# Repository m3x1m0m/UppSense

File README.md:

UppSense17- Open Source sensor for chemical analysis based on fuoresence.
 
## Hardware

The hardware consists out of three PCBs so far: An analog PCB, a digital PCB and an active Backplane. Two PCBs are developed with KiCAD. One is developed with Altium.

A transimpedance amplifier is used to convert light into a voltage. With a
second stage this voltage is amplified. Both outputs are available for the ADC. 

On the digital board there is besides an ESP8266, an ADC, a DAC and a temperature
sensor. The DAC is needed to steer the LED driver circuit, that excites the
sample. 
 
## Software

The software is written in C++ leveraging the
[Sming](https://github.com/SmingHub/Sming) framework. This enables IoT
applications very easily.

In the UML diagram above it is examplarily shown how the software works. Providers
and receivers can be tied together in pairs to enable an easy way to exchange
data. 

[Software Documentation](http://uppsense.eu/swdoc/)

## Web & Contact
Website: www.uppsense.eu | Email: contact@uppsense.eu

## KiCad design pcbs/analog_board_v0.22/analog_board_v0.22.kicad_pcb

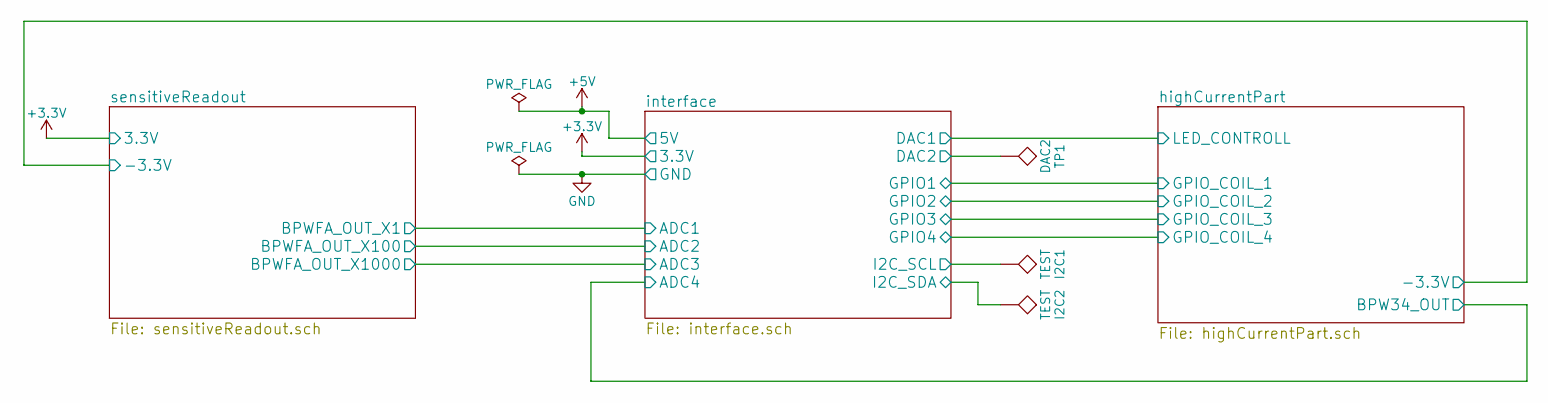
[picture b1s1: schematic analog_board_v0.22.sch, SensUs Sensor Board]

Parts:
I2C1, I2C2: TEST; TP_SMD_quadr_1mm
TP1: DAC2; TP_SMD_quadr_1mm

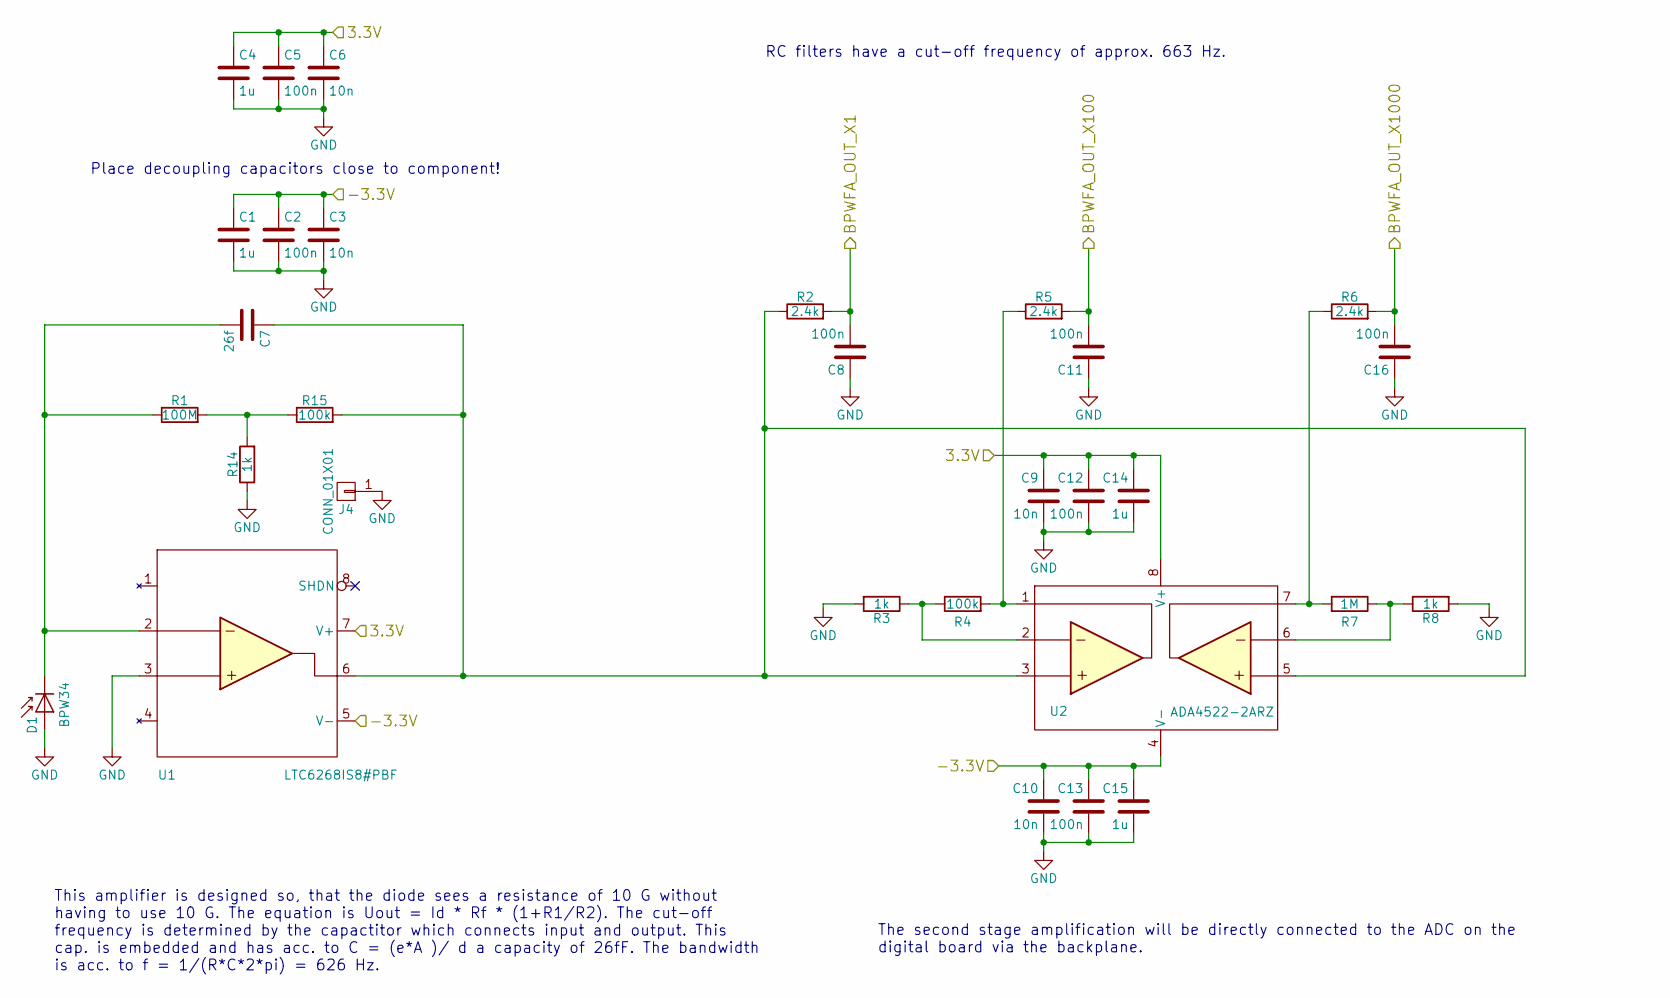
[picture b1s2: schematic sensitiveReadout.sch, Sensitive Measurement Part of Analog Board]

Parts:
C1, C4, C14, C15: 1u; R_0805; Farnell 2496946
C2, C5, C8, C11, C12, C13, C16: 100n; R_0805; Farnell 499687
C3, C6, C9, C10: 10n; R_0805; Farnell 1414662
C7: 26f; EMBEDDED_CAP_1mm
D1: BPW34; BPW34FA_w_Silks; Farnell 1045425
J4: CONN_01X01; GuardConnector
R1: 100M; R_0805_W_Silks; Farnell 9236511
R2, R5, R6: 2.4k; R_0805; Farnell 2502703
R3, R8: 1k; R_0805; Farnell 9237496
R4: 100k; R_0805; Farnell 2447551
R7: 1M; R_0805; Farnell 1576507
R14: 1k; R_0805_W_Silks; Farnell 9237496
R15: 100k; R_0805_W_Silks; Farnell 2447551
U1: LTC6268IS8#PBF; SOIC-8-N-W-Silks; Farnell 2464182
U2: ADA4522-2ARZ; SOIC-8-N; Farnell 2505560

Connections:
+3V3: C4.1, C5.1, C6.1, C9.1, C12.1, C14.1, U1.7 (V+), U2.8 (V+); also elsewhere on the board
/highCurrentPart/-3.3V: C1.1, C2.1, C3.1, C10.1, C13.1, C15.1, U1.5 (V-), U2.4 (V-); also elsewhere on the board
/interface/ADC1: C8.2, R2.2; also elsewhere on the board
/interface/ADC2: C11.2, R5.2; also elsewhere on the board
/interface/ADC3: C16.2, R6.2; also elsewhere on the board
GND: C1.2, C2.2, C3.2, C4.2, C5.2, C6.2, C8.1, C9.2, C10.2, C11.1, C12.2, C13.2, C14.2, C15.2, C16.1, D1.2 (A), J4.1, R3.2, R8.2, R14.1, U1.3; also elsewhere on the board
unnamed: C7.1, R2.1, R15.2, U1.6, U2.3, U2.5
unnamed: C7.2, D1.1 (K), R1.1, U1.2
unnamed: R1.2, R14.2, R15.1
unnamed: R3.1, R4.1, U2.2
unnamed: R4.2, R5.1, U2.1
unnamed: R6.1, R7.2, U2.7
unnamed: R7.1, R8.1, U2.6

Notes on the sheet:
Place decoupling capacitors close to component!
The second stage amplification will be directly connected to the ADC on the digital board via the backplane.
RC filters have a cut-off frequency of approx. 663 Hz.
This amplifier is designed so, that the diode sees a resistance of 10 G without having to use 10 G. The equation is Uout = Id * Rf * (1+R1/R2). The cut-off frequency is determined by the capactitor which connects input and output. This cap. is embedded and has acc. to C = (e*A )/ d a capacity of 26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

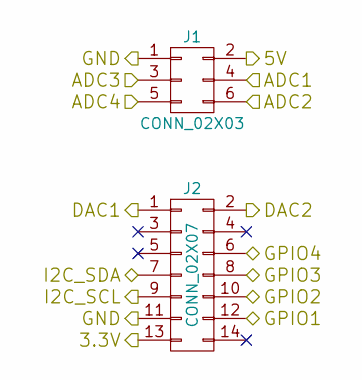
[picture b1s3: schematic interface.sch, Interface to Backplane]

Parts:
J1: CONN_02X03; Pin_Header_Angled_2x03_Pitch2.54mm
J2: CONN_02X07; Pin_Header_Angled_2x07_Pitch2.54mm

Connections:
+3V3: J2.13; also elsewhere on the board
+5V: J1.2; also elsewhere on the board
/interface/ADC1: J1.4; also elsewhere on the board
/interface/ADC2: J1.6; also elsewhere on the board
/interface/ADC3: J1.3; also elsewhere on the board
/interface/ADC4: J1.5; also elsewhere on the board
/interface/DAC1: J2.1; also elsewhere on the board
/interface/DAC2: J2.2; also elsewhere on the board
/interface/GPIO1: J2.12; also elsewhere on the board
/interface/GPIO2: J2.10; also elsewhere on the board
/interface/GPIO3: J2.8; also elsewhere on the board
/interface/GPIO4: J2.6; also elsewhere on the board
/interface/I2C_SCL: J2.9; also elsewhere on the board
/interface/I2C_SDA: J2.7; also elsewhere on the board
GND: J1.1, J2.11; also elsewhere on the board

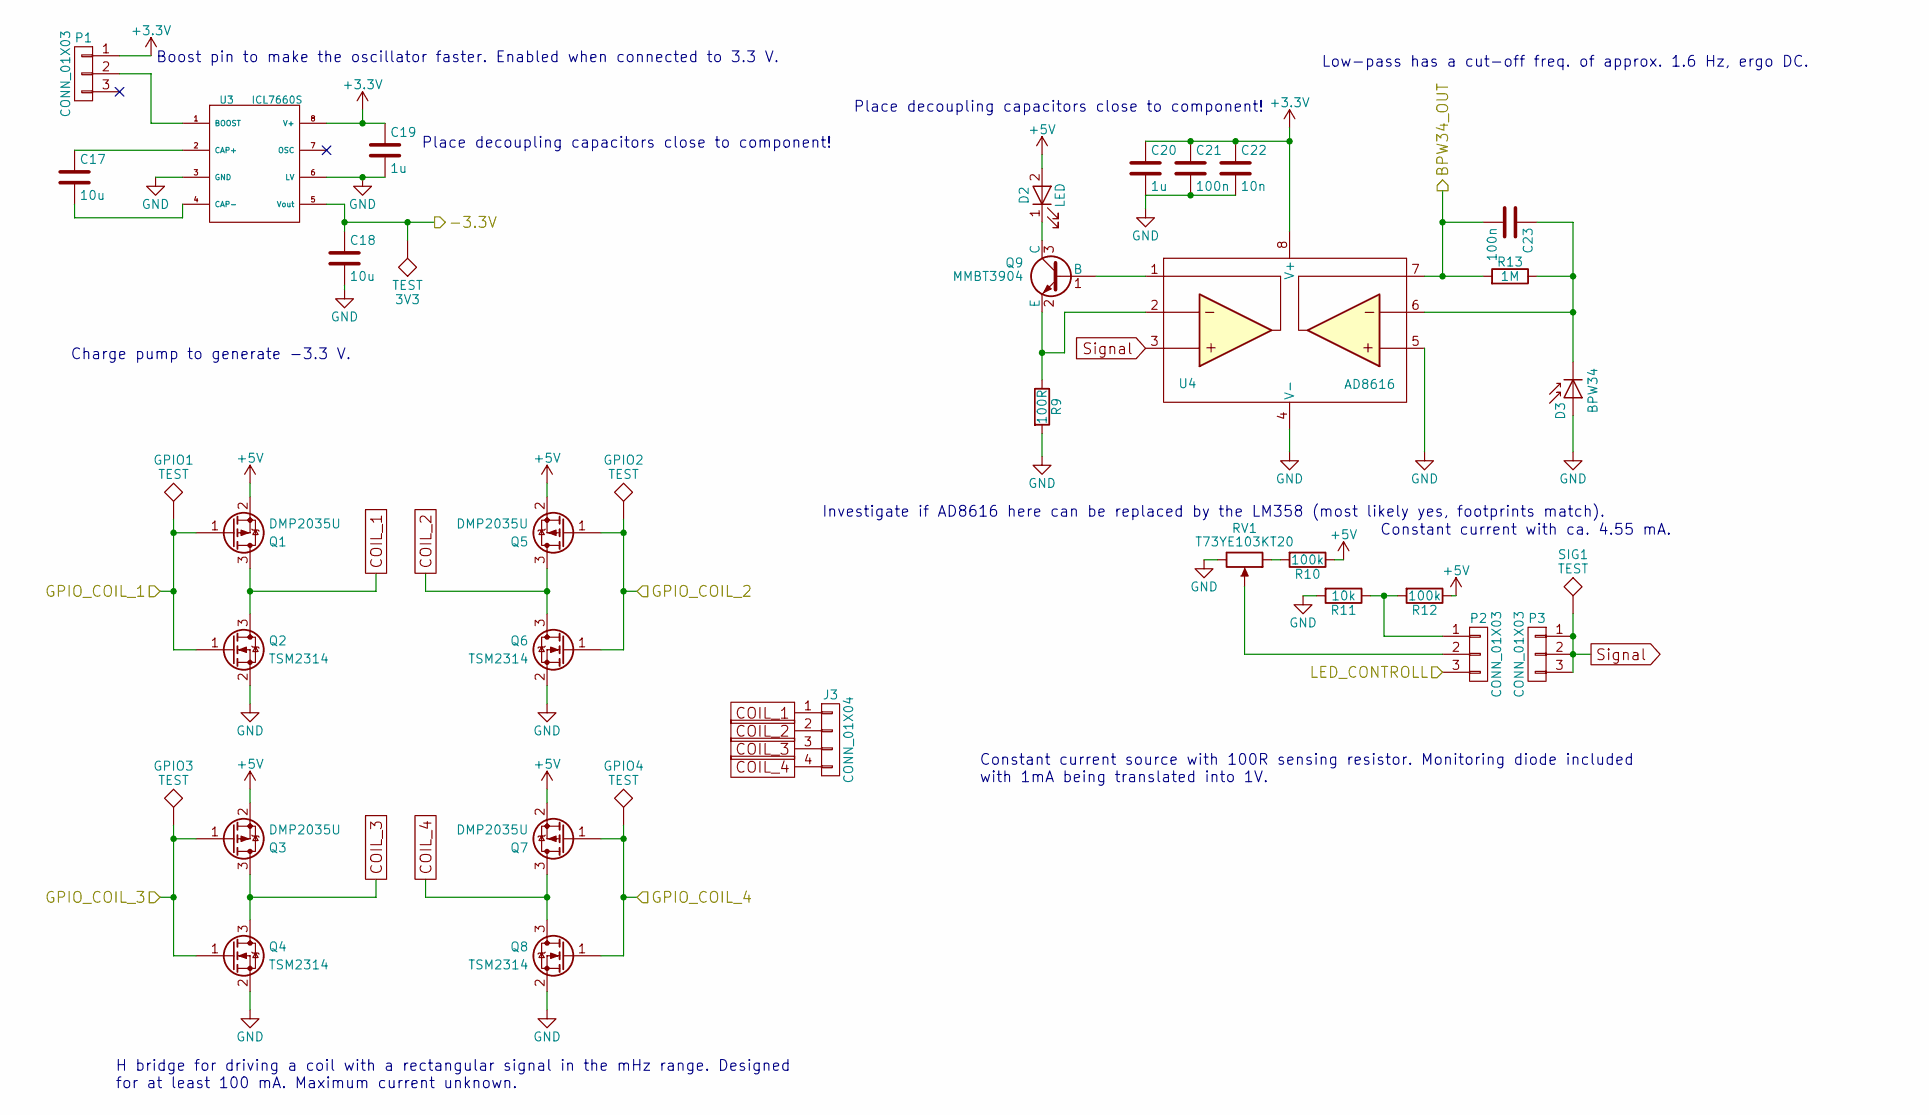
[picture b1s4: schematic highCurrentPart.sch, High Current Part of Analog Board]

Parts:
3V3: TEST; TP_SMD_quadr_1mm
C17, C18: 10u; R_0805; Farnell 1833812
C19: 1u; R_0805; Farnell 1845751
C20: 1u; R_0805; Farnell 2496946
C21, C23: 100n; R_0805; Farnell 499687
C22: 10n; R_0805; Farnell 1414662
D2: LED; LED_D5.0mm
D3: BPW34; BPW34FA; Farnell 1045425
GPIO1, GPIO2, GPIO3, GPIO4: TEST; TP_SMD_quadr_1mm
J3: CONN_01X04; LED_CONN_1.25_PITCH
P1, P2, P3: CONN_01X03; Samtec-PHT-1-3-01-L-S
Q1, Q3, Q5, Q7: DMP2035U; SOT-23; Farnell 2061419
Q2, Q4, Q6, Q8: TSM2314; SOT-23; Farnell 1864589
Q9: MMBT3904; SOT-23; Farnell 1757935
R9: 100R; R_0805; Farnell 1632456
R10, R12: 100k; R_0805; Farnell 2447551
R11: 10k; R_0805; Farnell 9237755
R13: 1M; R_0805; Farnell 1576507
RV1: T73YE103KT20; Vishay_T73YE103KT20; Farnell 2550676
SIG1: TEST; TP_SMD_quadr_1mm
U3: ICL7660S; SOIC-8-N; Farnell 1561969
U4: AD8616; SOIC-8-N; Farnell 1581952

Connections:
+3V3: C19.1, C20.1, C21.1, C22.1, P1.1, U3.8 (V+), U4.8 (V+); also elsewhere on the board
+5V: D2.2 (A), Q1.2 (S), Q3.2 (S), Q5.2 (S), Q7.2 (S), R10.1, R12.1; also elsewhere on the board
/highCurrentPart/-3.3V: 3V3.1, C18.1, U3.5 (Vout); also elsewhere on the board
/interface/ADC4: C23.2, R13.2, U4.7; also elsewhere on the board
/interface/DAC1: P2.3; also elsewhere on the board
/interface/GPIO1: GPIO1.1, Q1.1 (G), Q2.1 (G); also elsewhere on the board
/interface/GPIO2: GPIO2.1, Q5.1 (G), Q6.1 (G); also elsewhere on the board
/interface/GPIO3: GPIO3.1, Q3.1 (G), Q4.1 (G); also elsewhere on the board
/interface/GPIO4: GPIO4.1, Q7.1 (G), Q8.1 (G); also elsewhere on the board
COIL_1: J3.1, Q1.3 (D), Q2.3 (D)
COIL_2: J3.2, Q5.3 (D), Q6.3 (D)
COIL_3: J3.3, Q3.3 (D), Q4.3 (D)
COIL_4: J3.4, Q7.3 (D), Q8.3 (D)
GND: C18.2, C19.2, C20.2, C21.2, C22.2, D3.2 (A), Q2.2 (S), Q4.2 (S), Q6.2 (S), Q8.2 (S), R9.2, R11.2, RV1.3, U3.3 (GND), U3.6 (LV), U4.4 (V-), U4.5; also elsewhere on the board
unnamed: C17.1, U3.2 (CAP+)
unnamed: C17.2, U3.4 (CAP-)
unnamed: C23.1, D3.1 (K), R13.1, U4.6
unnamed: D2.1 (K), Q9.3 (C)
unnamed: P1.2, U3.1 (BOOST)
unnamed: P2.1, R11.1, R12.2
unnamed: P2.2, RV1.2
unnamed: Q9.1 (B), U4.1
unnamed: Q9.2 (E), R9.1, U4.2
unnamed: R10.2, RV1.1
Signal: P3.1, P3.2, P3.3, SIG1.1, U4.3; also elsewhere on the board

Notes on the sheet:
Place decoupling capacitors close to component!
Constant current source with 100R sensing resistor. Monitoring diode included with 1mA being translated into 1V.
Constant current with ca. 4.55 mA.
H bridge for driving a coil with a rectangular signal in the mHz range. Designed for at least 100 mA. Maximum current unknown.
Boost pin to make the oscillator faster. Enabled when connected to 3.3 V.
Charge pump to generate -3.3 V.
Low-pass has a cut-off freq. of approx. 1.6 Hz, ergo DC.
Investigate if AD8616 here can be replaced by the LM358 (most likely yes, footprints match).

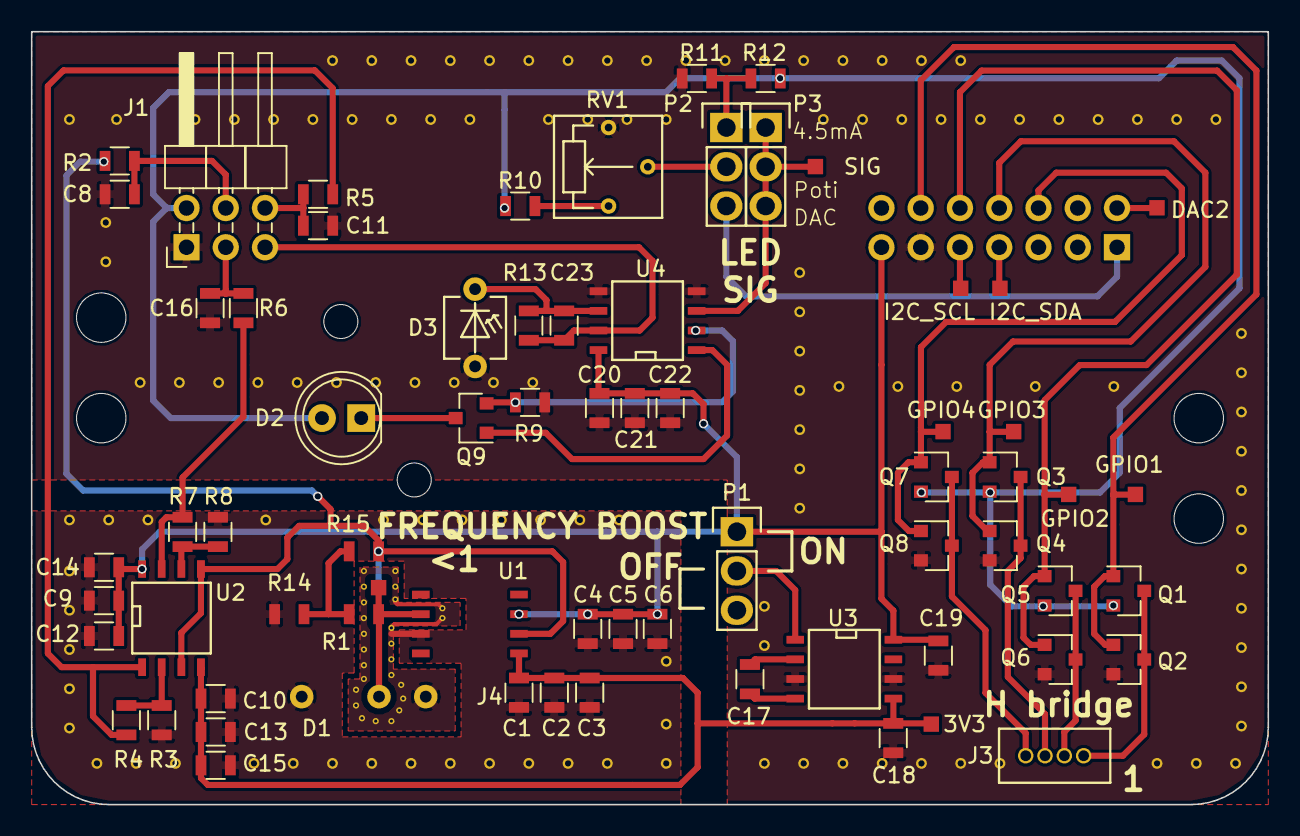
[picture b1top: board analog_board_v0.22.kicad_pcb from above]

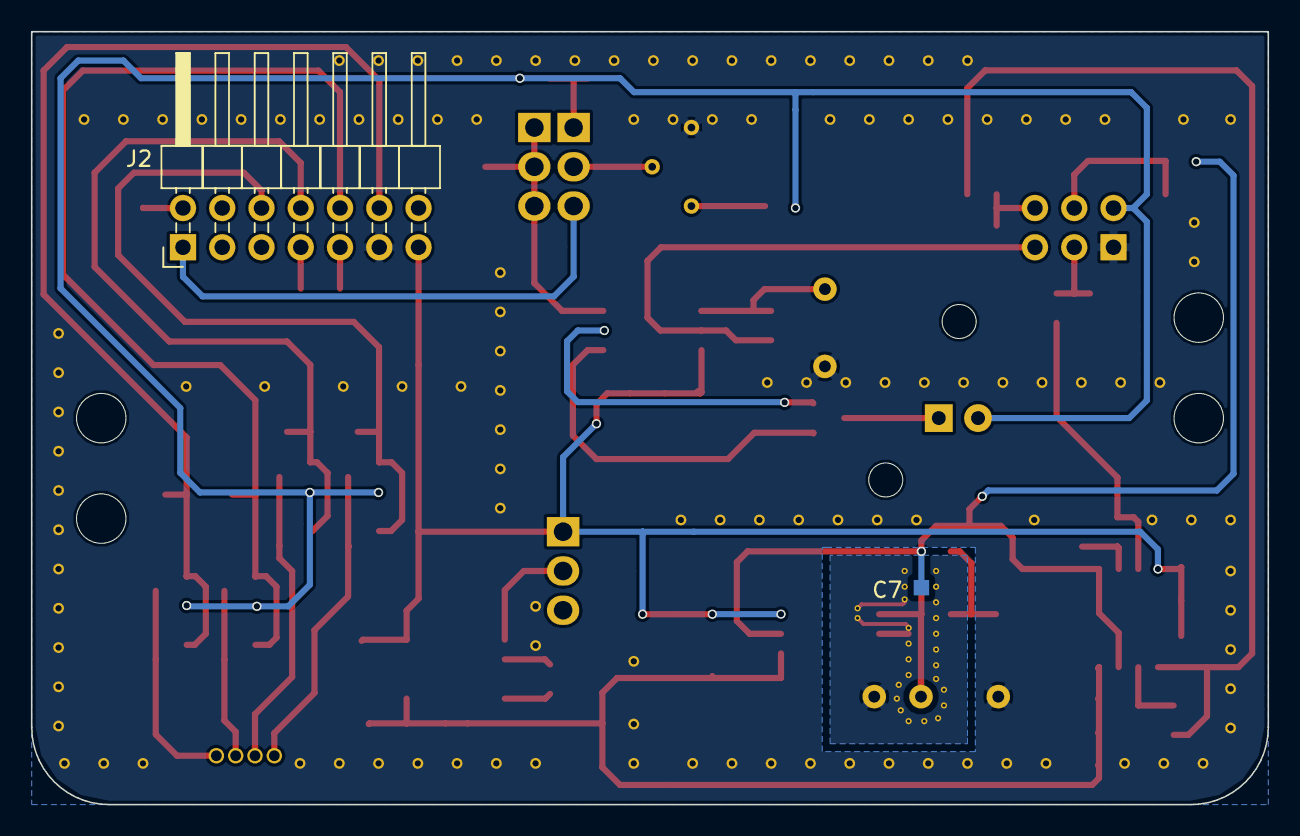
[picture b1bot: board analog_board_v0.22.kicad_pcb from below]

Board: 2 copper layers, 80.0 x 50.0 mm, 71 parts (2 on the bottom side), 38 nets.

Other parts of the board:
DAC2: DAC2; TP_SMD_quadr_1mm
I2C_SCL, I2C_SDA: TEST; TP_SMD_quadr_1mm
SIG: TEST; TP_SMD_quadr_1mm

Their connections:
/interface/DAC2: DAC2.1; also elsewhere on the board
/interface/I2C_SCL: I2C_SCL.1; also elsewhere on the board
/interface/I2C_SDA: I2C_SDA.1; also elsewhere on the board
Signal: SIG.1; also elsewhere on the board

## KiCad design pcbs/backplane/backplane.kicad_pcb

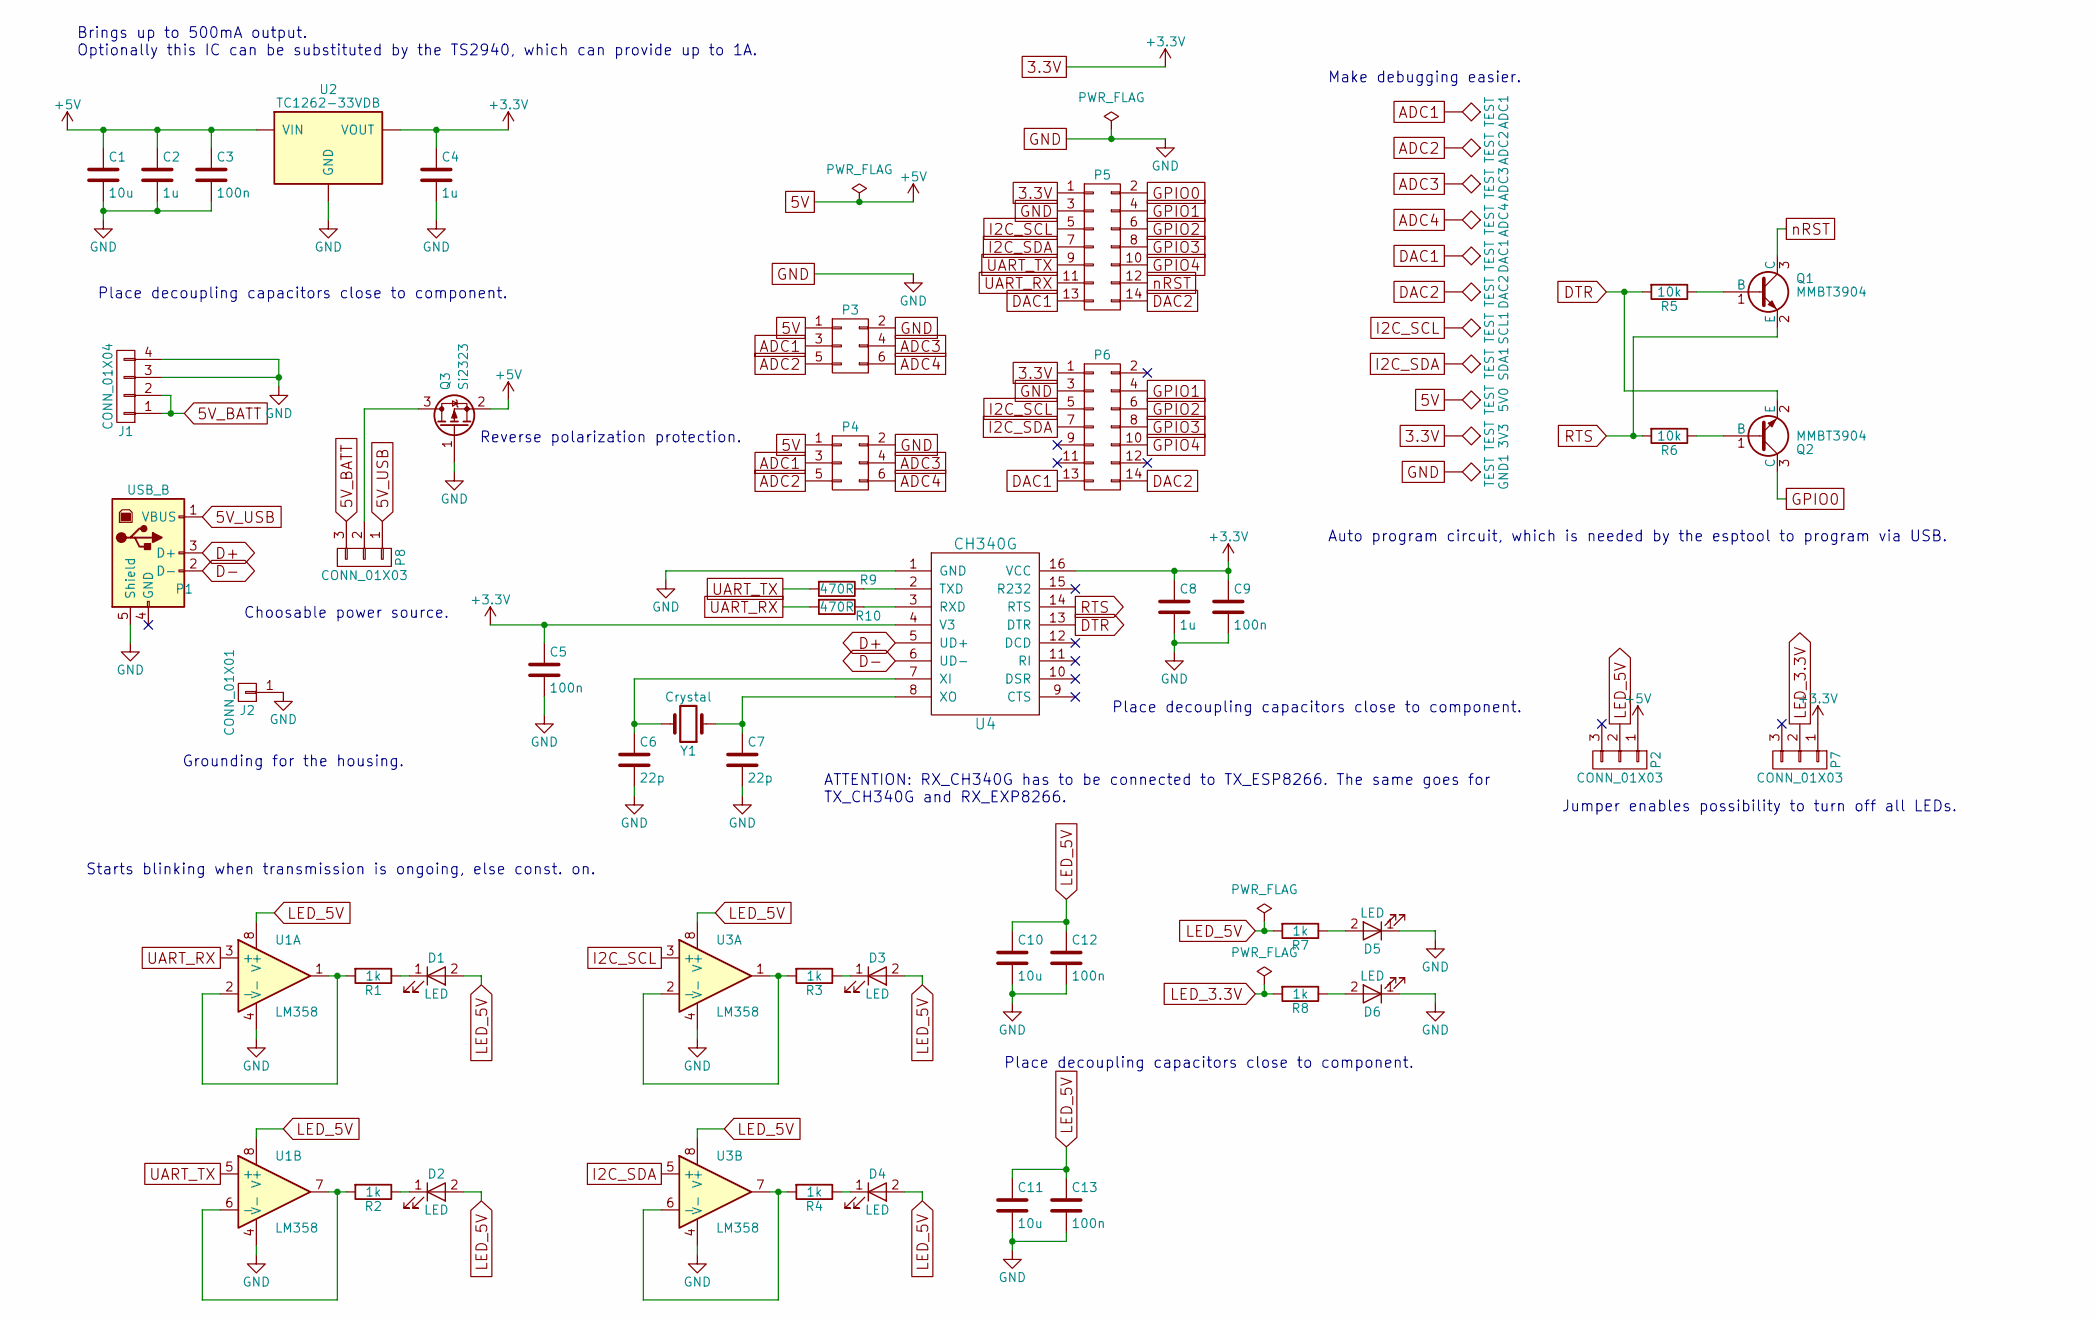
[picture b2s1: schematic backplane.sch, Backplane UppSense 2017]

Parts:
3V3, 5V0: TEST; TP_SMD_quadr_1mm
ADC1, ADC2, ADC3, ADC4: TEST; TP_SMD_quadr_1mm
C1, C10, C11: 10u; R_0805; Farnell 1833812
C2, C4, C8: 1u; R_0805; Farnell 2496946
C3, C5, C9, C12, C13: 100n; R_0805; Farnell 499687
C6, C7: 22p; R_0805; Farnell 1759489
D1, D2, D3, D4, D5, D6: LED; LED_0805; Farnell 1581242
DAC1, DAC2: TEST; TP_SMD_quadr_1mm
GND1: TEST; TP_SMD_quadr_3mm
J1: CONN_01X04; LED_CONN_1.25_PITCH
J2: CONN_01X01; Samtec-PHT-1-1-01-L-S
P1: USB_B; ZX62D-B-5P8(30); Farnell 2554980
P2, P7, P8: CONN_01X03; Samtec-PHT-1-3-01-L-S
P3, P4: CONN_02X03; Pin_Header_Straight_2x03
P5, P6: CONN_02X07; Pin_Header_Straight_2x07
Q1, Q2: MMBT3904; SOT-23; Farnell 2535650
Q3: Si2323; SOT-23; Farnell 1470106
R1, R2, R3, R4, R7, R8: 1k; R_0805; Farnell 9237496
R5, R6: 10k; R_0805; Farnell 9237755
R9, R10: 470R; R_0805; Farnell 2447662
SCL1: TEST; TP_SMD_quadr_1mm
SDA1: TEST; TP_SMD_quadr_1mm
U1, U3: LM358; SOIC-8-N; Farnell 1564331
U2: TC1262-33VDB; SOT-223; Farnell 1296594
U4: CH340G; SO-16-N
Y1: Crystal; Crystal_SMD_HC49-SD; Farnell 9713344

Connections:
3.3V: 3V3.1, C4.1, C5.1, C8.1, C9.1, P5.1, P6.1, P7.1, U2.3 (VOUT), U4.4 (V3), U4.16 (VCC)
5V: 5V0.1, C1.1, C2.1, C3.1, P2.1, P3.1, P4.1, Q3.2 (S), U2.1 (VIN); also elsewhere on the board
5V_BATT: J1.1, J1.2, P8.3
5V_USB: P1.1 (VBUS), P8.1
ADC1: ADC1.1, P3.3, P4.3
ADC2: ADC2.1, P3.5, P4.5
ADC3: ADC3.1, P3.4, P4.4
ADC4: ADC4.1, P3.6, P4.6
D+: P1.3 (D+), U4.5 (UD+)
D-: P1.2 (D-), U4.6 (UD-)
DAC1: DAC1.1, P5.13, P6.13
DAC2: DAC2.1, P5.14, P6.14
DTR: Q2.2 (E), R5.2, U4.13 (DTR)
GND: C1.2, C2.2, C3.2, C4.2, C5.2, C6.2, C7.2, C8.2, C9.2, C10.2, C11.2, C12.2, C13.2, D5.1 (K), D6.1 (K), GND1.1, J1.3, J1.4, J2.1, P1.5 (Shield), P3.2, P4.2, P5.3, P6.3, Q3.1 (G), U1.4 (V-), U2.2 (GND), U2.4 (GND), U3.4 (V-), U4.1 (GND); also elsewhere on the board
GPIO0: P5.2, Q2.3 (C)
GPIO1: P5.4, P6.4
GPIO2: P5.6, P6.6
GPIO3: P5.8, P6.8
GPIO4: P5.10, P6.10
I2C_SCL: P5.5, P6.5, SCL1.1, U3.3 (+); also elsewhere on the board
I2C_SDA: P5.7, P6.7, SDA1.1, U3.5 (+); also elsewhere on the board
LED_3.3V: P7.2, R8.2
LED_5V: C10.1, C11.1, C12.1, C13.1, D1.2 (A), D2.2 (A), D3.2 (A), D4.2 (A), P2.2, R7.2, U1.8 (V+), U3.8 (V+)
unnamed: C6.1, U4.7 (XI), Y1.2
unnamed: C7.1, U4.8 (XO), Y1.1
unnamed: D1.1 (K), R1.1
unnamed: D2.1 (K), R2.1
unnamed: D3.1 (K), R3.1
unnamed: D4.1 (K), R4.1
unnamed: D5.2 (A), R7.1
unnamed: D6.2 (A), R8.1
unnamed: P8.2, Q3.3 (D)
unnamed: Q1.1 (B), R5.1
unnamed: Q2.1 (B), R6.1
unnamed: R1.2, U1.1, U1.2 (-)
unnamed: R2.2, U1.6 (-), U1.7
unnamed: R3.2, U3.1, U3.2 (-)
unnamed: R4.2, U3.6 (-), U3.7
unnamed: R9.1, U4.2 (TXD)
unnamed: R10.1, U4.3 (RXD)
RTS: Q1.2 (E), R6.2, U4.14 (RTS)
UART_RX: P5.11, R10.2, U1.3 (+)
UART_TX: P5.9, R9.2, U1.5 (+)
nRST: P5.12, Q1.3 (C)

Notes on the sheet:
Place decoupling capacitors close to component.
Brings up to 500mA output. Optionally this IC can be substituted by the TS2940, which can provide up to 1A.
Auto program circuit, which is needed by the esptool to program via USB.
Starts blinking when transmission is ongoing, else const. on.
Make debugging easier.
Jumper enables possibility to turn off all LEDs.
ATTENTION: RX_CH340G has to be connected to TX_ESP8266. The same goes for TX_CH340G and RX_EXP8266.
Reverse polarization protection.
Choosable power source.
Grounding for the housing.

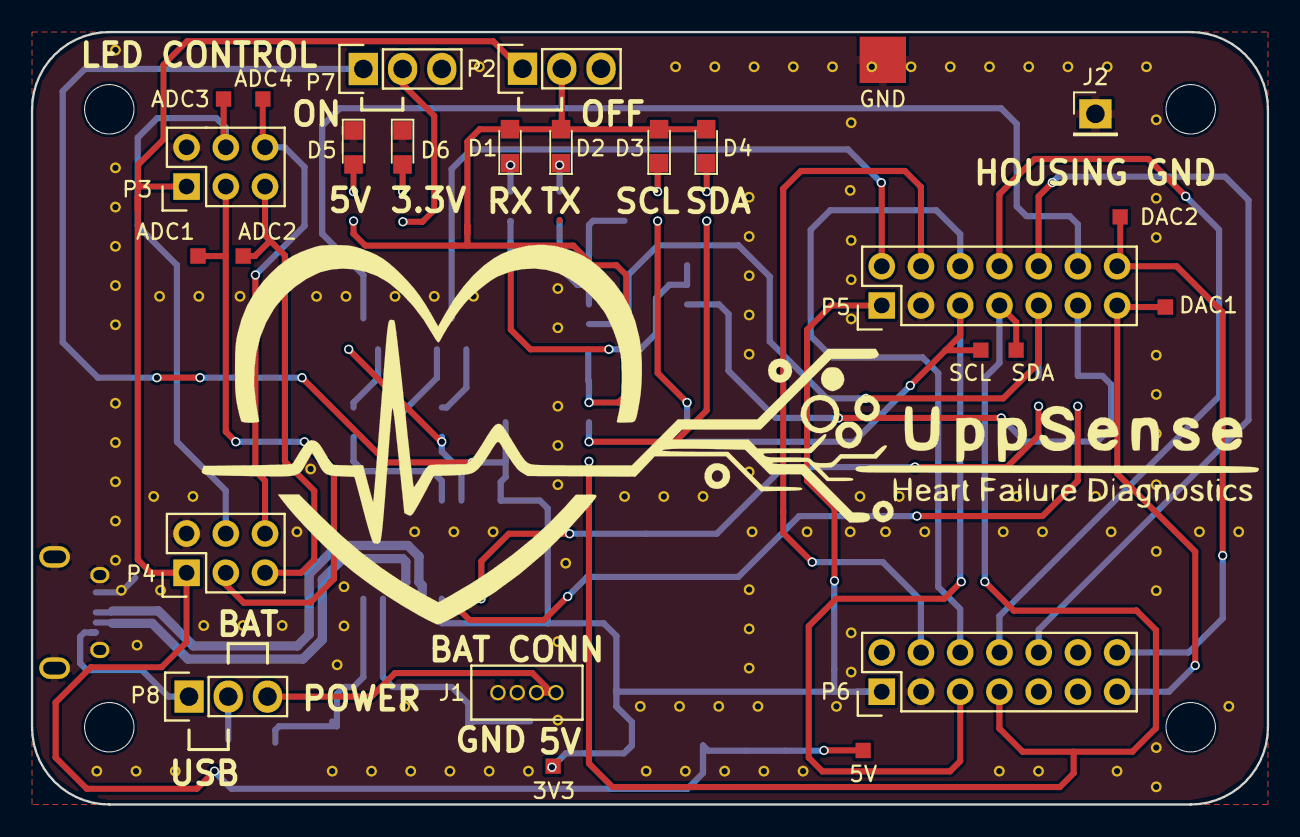
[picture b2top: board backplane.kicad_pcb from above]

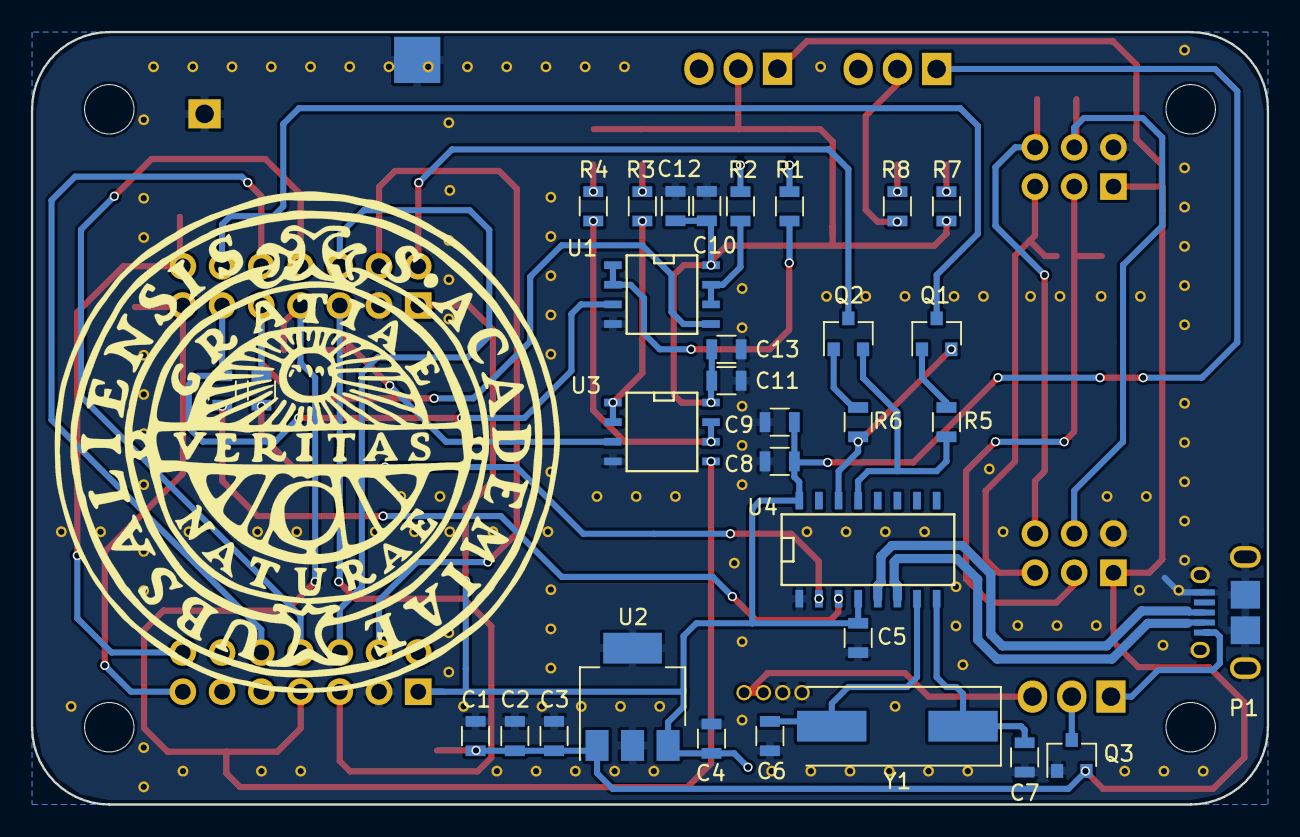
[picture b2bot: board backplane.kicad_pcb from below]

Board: 2 copper layers, 80.0 x 50.0 mm, 59 parts (32 on the bottom side), 44 nets.

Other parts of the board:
5V: TEST; TP_SMD_quadr_1mm
GND: TEST; TP_SMD_quadr_3mm
SCL: TEST; TP_SMD_quadr_1mm
SDA: TEST; TP_SMD_quadr_1mm

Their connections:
5V: 5V.1; also elsewhere on the board
GND: GND.1; also elsewhere on the board
I2C_SCL: SCL.1; also elsewhere on the board
I2C_SDA: SDA.1; also elsewhere on the board

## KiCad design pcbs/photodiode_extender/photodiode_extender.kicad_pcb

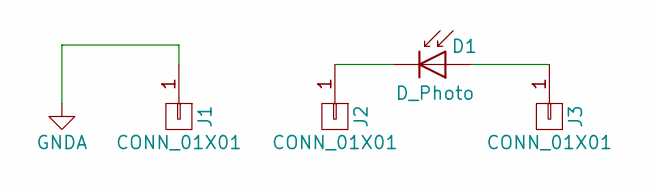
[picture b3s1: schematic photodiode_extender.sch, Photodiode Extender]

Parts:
D1: D_Photo; BPW34FA_w_Silks
J1, J2: CONN_01X01; Pin_Header_Angled_1x01_Pitch2.54mm_W_Silkscreen
J3: CONN_01X01; Pin_Header_Angled_1x01_Pitch2.54mm

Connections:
GNDA: J1.1
unnamed: D1.1 (K), J2.1
unnamed: D1.2 (A), J3.1

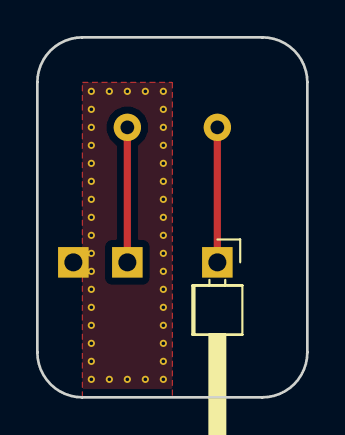
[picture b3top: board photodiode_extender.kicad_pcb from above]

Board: 2 copper layers, 15.0 x 20.0 mm, 4 parts (0 on the bottom side), 2 nets.

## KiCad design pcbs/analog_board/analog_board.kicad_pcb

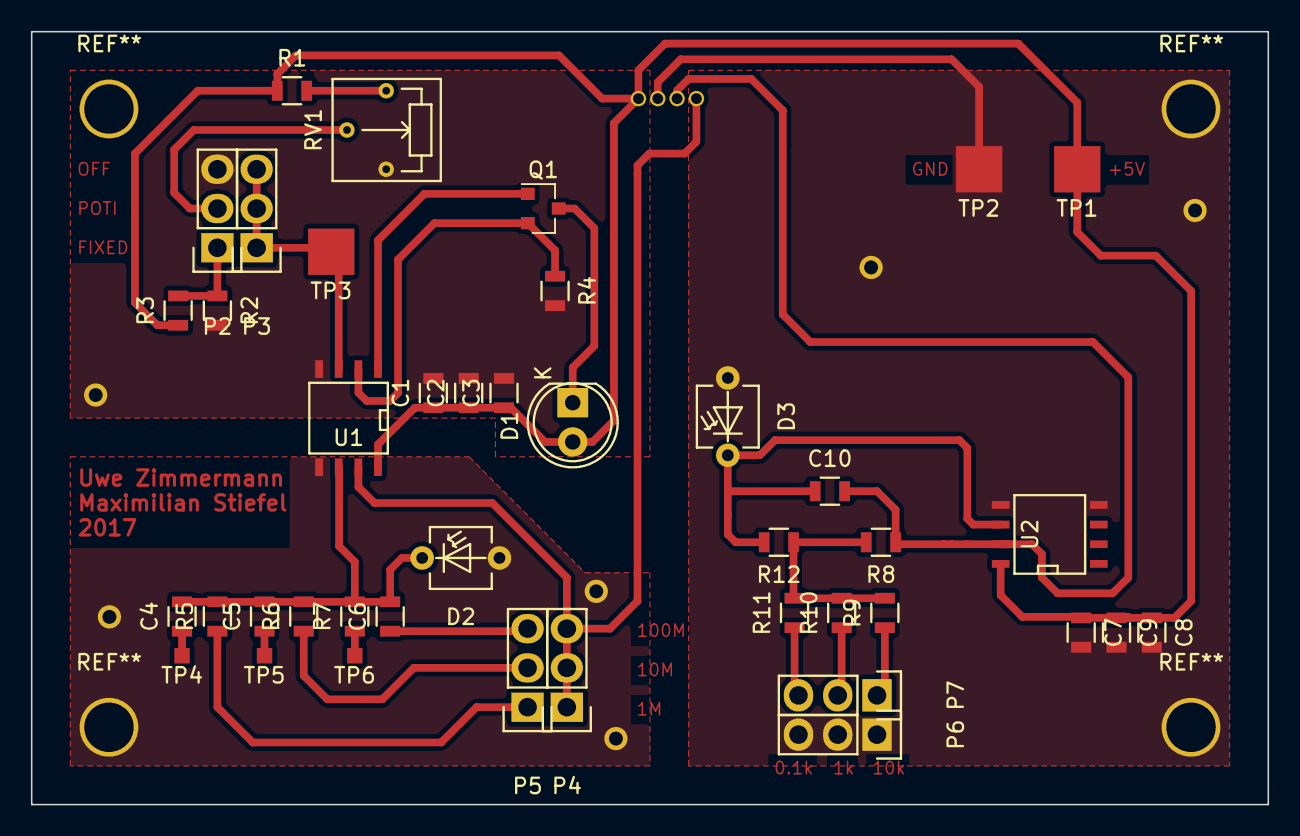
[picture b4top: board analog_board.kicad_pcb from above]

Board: 2 copper layers, 80.0 x 50.0 mm, 42 parts (1 on the bottom side), 20 nets.

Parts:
C1, C7: 1u; R_0805
C2, C8: 100n; R_0805
C3, C9: 10n; R_0805
C4: 100p; R_0805
C5: 10p; R_0805
C6, C10: 1p; R_0805
D1: LED; LED-5MM
D2, D3: BPW34; BPW34FA
P1: CONN_01X04; LED_CONN_1.25_PITCH
P2, P3, P4, P5, P6, P7: CONN_01X03; Samtec-PHT-1-3-01-L-S
Q1: MMBT3904; SOT-23
R1, R3, R8: 100k; R_0805
R2, R9: 10k; R_0805
R4: 100R; R_0805
R5: 1M; R_0805
R6, R12: 10M; R_0805
R7: 100M; R_0805
R10: 1K; R_0805
R11: 0.1k; R_0805
RV1: T73YE103KT20; Vishay_T73YE103KT20
TP1, TP2, TP3: TEST; TP_SMD_quadr_3mm
TP4, TP5, TP6: TEST; TP_SMD_quadr_1mm
U1, U2: AD8616; SOIC-8-N

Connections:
+5V: C1.1, C2.1, C3.1, C7.1, C8.1, C9.1, D1.2, P1.4, R1.1, R3.1, TP1.1, U1.8, U2.8
/highCurrent/BPW34_OUT: P1.1, P4.1, P4.2, P4.3, U1.7
/lowCurrent/BPW34FA_OUT: C10.2, P1.2, R8.1, U2.7
GND: C1.2, C2.2, C3.2, C7.2, C8.2, C9.2, D2.2, D3.2, P1.3, P2.3, P6.1, P6.2, P6.3, R2.2, R4.2, RV1.3, TP2.1, U1.4, U1.5, U2.4, U2.5
unnamed: C4.1, P5.1, R5.1, TP4.1
unnamed: C4.2, C5.2, C6.2, D2.1, R5.2, R6.2, R7.2, U1.6
unnamed: C5.1, P5.2, R6.1, TP5.1
unnamed: C6.1, P5.3, R7.1, TP6.1
unnamed: C10.1, D3.1, R12.2, U2.6
unnamed: D1.1, Q1.3
unnamed: P2.1, R2.1, R3.2
unnamed: P2.2, RV1.2
unnamed: P7.1, R9.1
unnamed: P7.2, R10.1
unnamed: P7.3, R11.1
unnamed: Q1.1, U1.1
unnamed: Q1.2, R4.1, U1.2
unnamed: R1.2, RV1.1
unnamed: R8.2, R9.2, R10.2, R11.2, R12.1
Signal: P3.1, P3.2, P3.3, TP3.1, U1.3

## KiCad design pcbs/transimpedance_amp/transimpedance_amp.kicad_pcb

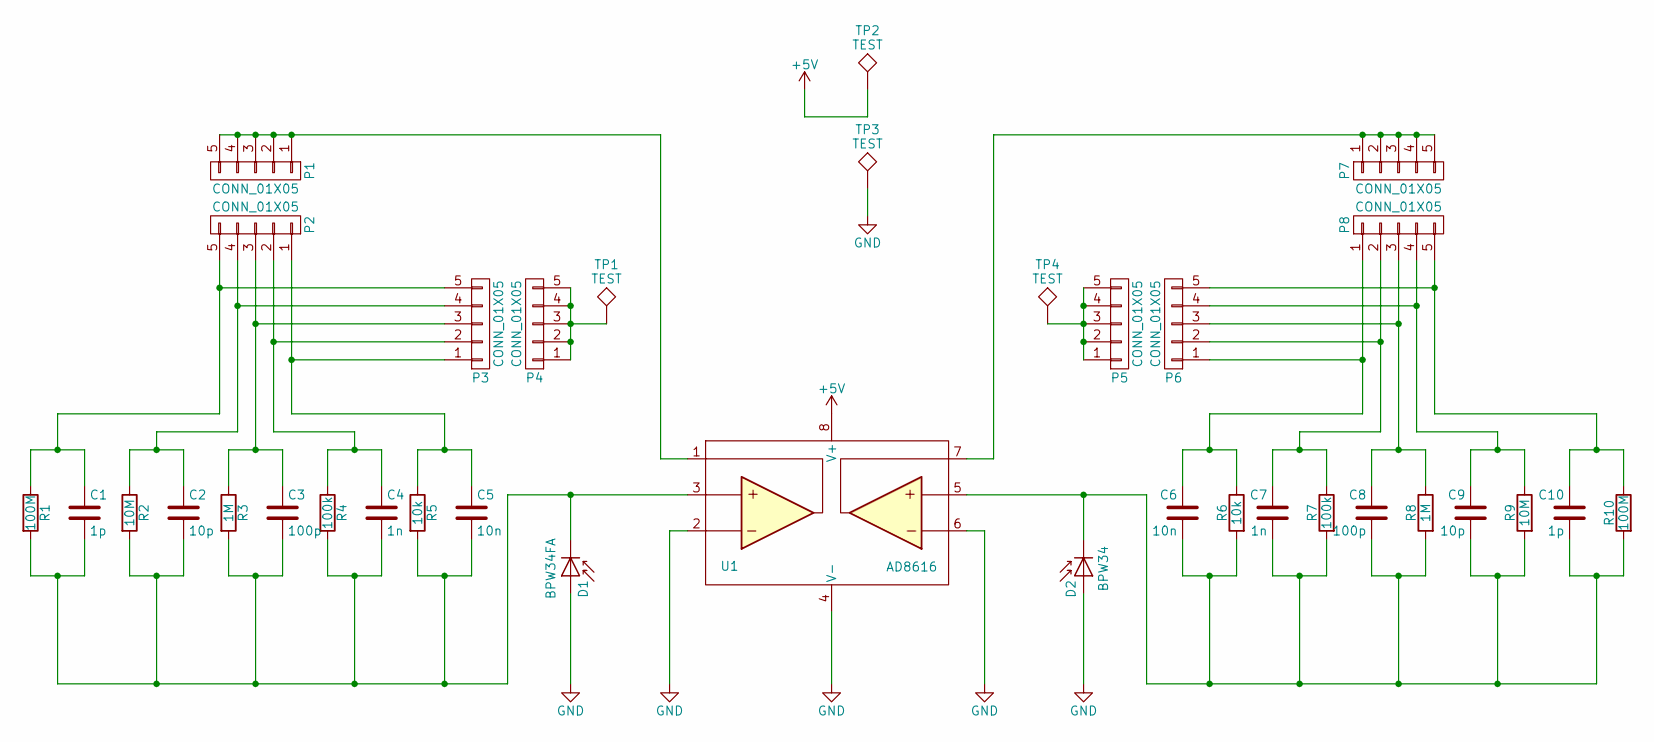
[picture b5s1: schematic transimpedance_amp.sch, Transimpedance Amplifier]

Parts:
C1, C10: 1p; R_0805
C2, C9: 10p; R_0805
C3, C8: 100p; R_0805
C4, C7: 1n; R_0805
C5, C6: 10n; R_0805
D1: BPW34FA
D2: BPW34; BPW34FA; Farnell 1045425
P1, P2, P3, P4, P5, P6, P7, P8: CONN_01X05; Pin_Header_Straight_1x05
R1, R10: 100M; R_0805
R2, R9: 10M; R_0805
R3, R8: 1M; R_0805
R4, R7: 100k; R_0805
R5, R6: 10k; R_0805
TP1, TP2, TP3, TP4: TEST; TP_SMD_quadr_3mm
U1: AD8616; SOIC-8-N; Farnell AD8616ARZ

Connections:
+5V: TP2.1, U1.8 (V+); also elsewhere on the board
GND: D1.2 (A), D2.2 (A), TP3.1, U1.2, U1.4 (V-), U1.6; also elsewhere on the board
unnamed: C1.1, P2.5, P3.5, R1.1
unnamed: C1.2, C2.2, C3.2, C4.2, C5.2, D1.1 (K), R1.2, R2.2, R3.2, R4.2, R5.2, U1.3
unnamed: C2.1, P2.4, P3.4, R2.1
unnamed: C3.1, P2.3, P3.3, R3.1
unnamed: C4.1, P2.2, P3.2, R4.1
unnamed: C5.1, P2.1, P3.1, R5.1
unnamed: C6.1, P6.1, P8.1, R6.1
unnamed: C7.1, P6.2, P8.2, R7.1
unnamed: C8.1, P6.3, P8.3, R8.1
unnamed: C9.1, P6.4, P8.4, R9.1
unnamed: C10.1, P6.5, P8.5, R10.1
unnamed: C6.2, C7.2, C8.2, C9.2, C10.2, D2.1 (K), R6.2, R7.2, R8.2, R9.2, R10.2, U1.5
unnamed: P1.1, P1.2, P1.3, P1.4, P1.5, U1.1
unnamed: P4.1, P4.2, P4.3, P4.4, P4.5, TP1.1
unnamed: P5.1, P5.2, P5.3, P5.4, P5.5, TP4.1
unnamed: P7.1, P7.2, P7.3, P7.4, P7.5, U1.7
